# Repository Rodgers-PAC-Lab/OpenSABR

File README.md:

# OpenSABR

OpenSABR stands for "Open-source System for Auditory Brainstem Response".
This repository was previously named "ABR2025".

## Introduction

This repository contains code to implement the ABR measuring system described
in [Gargiullo et al](https://www.biorxiv.org/content/10.64898/2025.12.17.694771v1), 
as well as the analysis scripts needed to replicate the figures in that paper.

The repository is structured as follows:
- `./` - The toplevel directory, containing this README file
- `./hardware_designs` - Design files, bill of materials, and other information about 
physically building the system.
- `./src/opensabr` - source code for analysis and GUI. Import like `import opensabr`
- `./src/opensabr/gui` - A Python module for running the graphical user interface (GUI) 
to take ABR data. It can be imported like `import opensabr.gui`. This code is 
run on a desktop PC connected to the ABR measuring system hardware.
- `./scripts` - A folder of demo scripts that generate the figures in the
paper, using data that we collected and have shared on Zenodo. These scripts 
are meant to be run one at a time, not imported and called by other scripts. 

## Requirements

We used Python 3.11. Newer versions may also work but we did not test them.
- pyproject.toml contains a list of the required dependencies
- requirements-lock.txt includes the exact versions we used

For the analysis scripts (but not the GUI), the following repository is 
required. It should be on your PYTHONPATH so that it can be imported using
the syntax `import my`.
- `git clone git@github.com:Rodgers-PAC-Lab/my.git`

## Instructions

To build the hardware, refer to the file `./hardware_designs/README.md` for finding code and design files, then refer to the file `OpenSABR Build Guide.pdf` for assembly instructions. 

To run the GUI and measure ABR, refer to the file `./src/opensabr/gui/README`.

To run the analysis scripts and regenerate the figures included in the paper,
refer to the file `./scripts/README`.

## Installation of OpenSABR

A note about our package management approach:
- Repositories that are install-able (i.e., using a method like `pip install` or `python setup.py`) are cloned into `~/installed`
- Repositories that need to be importable (like `import reponame`) but are not install-able are cloned into `~/dev`, which is a directory on `$PYTHONPATH`. Two examples of repositories like this are ABRA and Rodgers-PAC-Lab:my.git

The reason for this distinction is because it can cause errors to mix these two kinds of repositories in the same directory.

### Clone the OpenSABR repo

Run the following commands:

```
cd ~/installed
git clone git@github.com:Rodgers-PAC-Lab/OpenSABR
cd OpenSABR
```

Then pick one of the following installation approaches.
- Option A is easier and does not pin any versions of dependencies, so you will get the newest available
- Option B will download the exact versions of the repositories we used. This is mainly useful for reproducing our results exactly. This approach will only work on linux, since that is what we used.

### Option A: Typical install (no version pins)

```
conda create -n opensabr -c conda-forge python=3.11 pip ipython
conda activate opensabr
conda install -c conda-forge numpy scipy pandas matplotlib tqdm pyqt pyqtgraph pyserial pyarrow seaborn
pip install -e . --no-deps
```

### Option B: Reproducible install from lock (linux-64 only)

```
conda create -n opensabr --file opensabr-conda-lock.txt
conda activate opensabr
pip install -e . --no-deps
```

Now you have installed opensabr. Try `import opensabr` to be sure.

You can stop here if you all you want to do is run or use OpenSABR. You only have to continue if you want to reproduce the comparisons to ABRpresto and ABRA that were made in the paper.

## Installation of other ABR software used as a comparison in the paper

In the paper we also compared our analysis software to two others. If you wish to reproduce this comparison, you will need to install them.

- ABRA, installed into a separate conda environment called "abra"
- ABRpresto, installed into a separate conda environment called "abrpresto"

You do not need to install these others if you just want to run OpenSABR.

### Installing ABRpresto

This is an "install-able" module. 

#### Clone repo

Run the following to install our fork. Our demo scripts require the use of our fork, which contains only minor modifications.

```
cd ~/installed 
git clone git@github.com:Rodgers-PAC-Lab/ABRpresto # our fork
cd ABRpresto
git checkout dev # our branch with fixes
```

Then pick one of the following installation approaches, A (flexible) or B (reproducible), analogous to the options above.

#### Option A: Typical install (no version pins)

```
conda create -n abrpresto -c conda-forge python=3.11 ipython pip
conda activate abrpresto
conda install -c conda-forge numpy scipy pandas matplotlib setuptools_scm pyarrow tqdm
pip install -e . --no-deps
```

#### Option B: Reproducible install from lock (linux-64 only)

```
conda create -n abrpresto --file abrpresto-conda-lock.txt
conda activate abrpresto
pip install -e . --no-deps
```

Now ABRpresto should be installed. Check with `import abrpresto`

### Installing ABRA

This is not an "install-able" module, but it is importable, so it need to go on PYTHONPATH.

#### Clone repo (must be under ~/dev or some location on PYTHONPATH)

```
cd ~/dev
git clone git@github.com:Rodgers-PAC-Lab/abranalysis # our fork
cd abranalysis
git checkout dev # our branch with fixes
```

As above, pick Option A or B.

#### Option A: Typical install (no version pins)

```
conda create -n abra -c conda-forge python=3.11 ipython pip
conda activate abra
conda install -c conda-forge numpy scipy pandas scikit-learn pytorch=*=cpu* keras tensorflow streamlit easydict "altair<5" pyarrow matplotlib tqdm
conda env config vars set PYTHONPATH=$HOME/dev
conda deactivate && conda activate abra   # reload so PYTHONPATH takes effect
```

#### Option B: Reproducible install from lock (linux-64 only)

```
conda create -n abra --file abra-conda-lock.txt
conda activate abra
conda env config vars set PYTHONPATH=$HOME/dev
conda deactivate && conda activate abra   # reload so PYTHONPATH takes effect
```

Now ABRA should be installed. Check with `import abranalyais`

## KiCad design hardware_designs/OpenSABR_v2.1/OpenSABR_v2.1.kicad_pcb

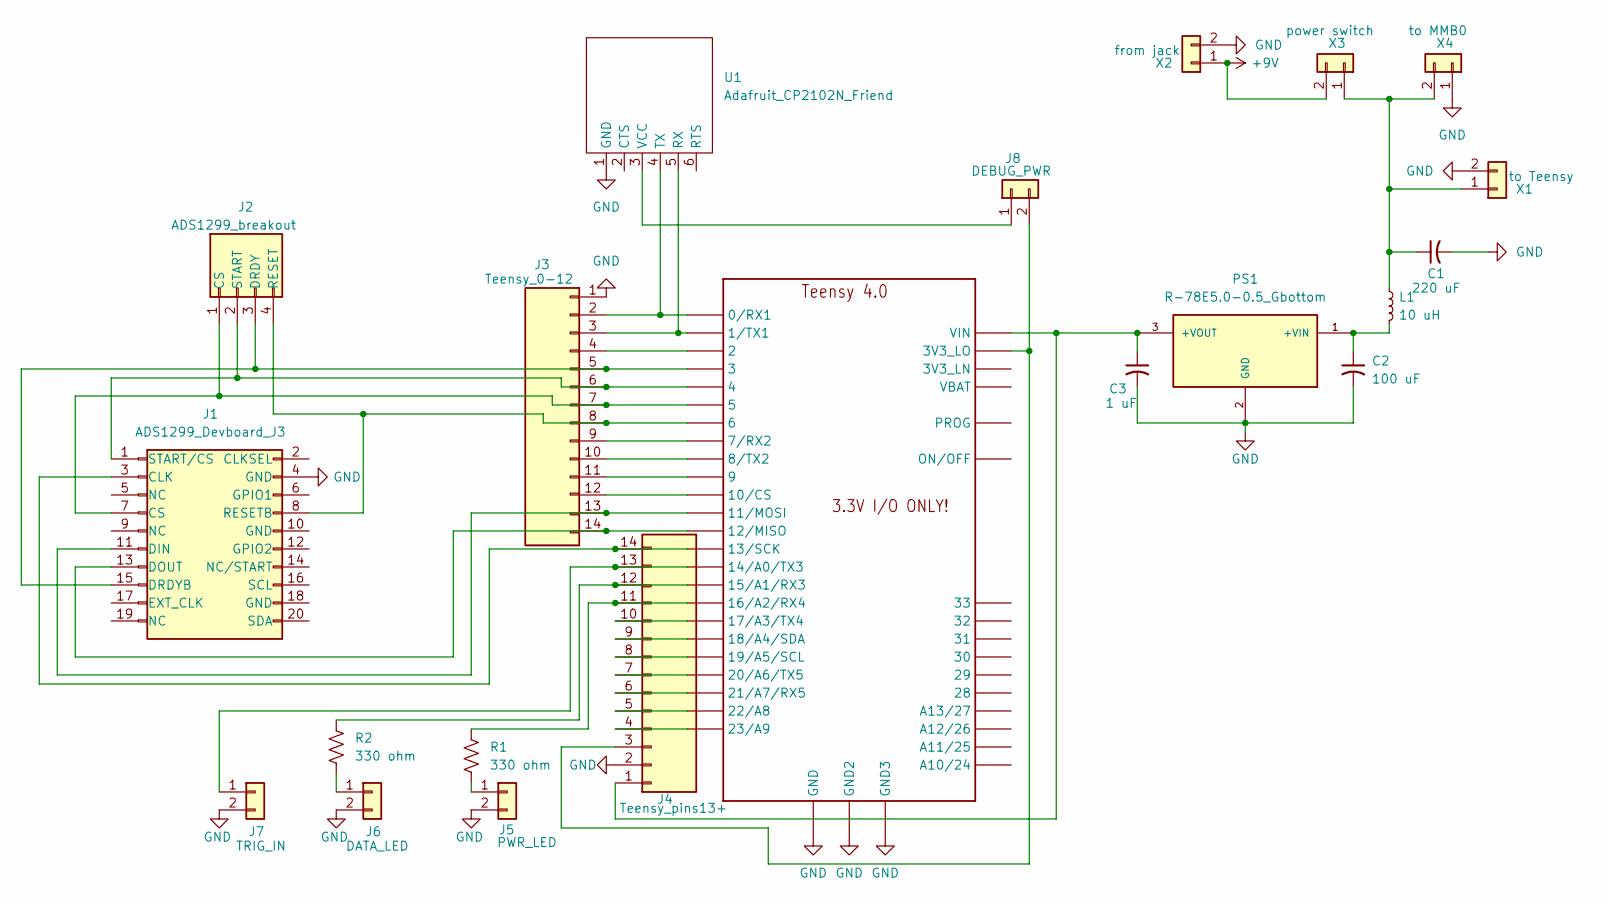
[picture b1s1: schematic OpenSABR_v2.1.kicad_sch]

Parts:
1: TEENSY_4.0_WITH_24-33
C1: 220 uF; CP_Radial_D10.0mm_P5.00mm
C2: 100 uF; CP_Radial_D8.0mm_P3.80mm
C3: 1 uF; CP_Radial_D7.5mm_P2.50mm
J1: ADS1299_Devboard_J3; IDC-Header_2x10_P2.54mm_Vertical
J2: ADS1299_breakout; PinSocket_1x04_P2.54mm_Vertical
J3: Teensy_0-12; PinHeader_1x14_P2.54mm_Vertical
J4: Teensy_pins13+; PinHeader_1x14_P2.54mm_Vertical
J5: PWR_LED; PinHeader_1x02_P2.54mm_Vertical
J6: DATA_LED; PinHeader_1x02_P2.54mm_Vertical
J7: TRIG_IN; PinHeader_1x02_P2.54mm_Vertical
J8: DEBUG_PWR; PinHeader_1x02_P2.54mm_Vertical
L1: 10 uH; L_Axial_L9.5mm_D4.0mm_P15.24mm_Horizontal_Fastron_SMCC
PS1: R-78E5.0-0.5_Gbottom; CONV_R-78E5.0-0.5; PARTREV v4
R1, R2: 330 ohm; R_Axial_DIN0207_L6.3mm_D2.5mm_P10.16mm_Horizontal
U1: Adafruit_CP2102N_Friend
X1: to Teensy; JST_XH_B2B-XH-A_1x02_P2.50mm_Vertical
X2: from jack; JST_XH_B2B-XH-A_1x02_P2.50mm_Vertical
X3: power switch; JST_XH_B2B-XH-A_1x02_P2.50mm_Vertical
X4: to MMB0; JST_XH_B2B-XH-A_1x02_P2.50mm_Vertical

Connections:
+9V: X2.1, X3.2
GND: 1.GND, 1.GND2, 1.GND3, C1.2, C2.2, C3.2, J1.4 (GND), J3.1, J4.2, J5.2, J6.2, J7.2, PS1.2 (GND), U1.1 (GND), X1.2, X2.2, X4.1
unnamed: 1.0/RX (0/RX1), J3.2, U1.4 (TX)
unnamed: 1.1/TX (1/TX1), J3.3, U1.5 (RX)
unnamed: 1.7 (7/RX2), J3.9
unnamed: 1.8 (8/TX2), J3.10
unnamed: 1.14/A0 (14/A0/TX3), J4.13, J7.1
unnamed: 1.15/A1 (15/A1/RX3), J4.12, R2.1
unnamed: 1.16/A2 (16/A2/RX4), J4.11, R1.1
unnamed: 1.17/A3 (17/A3/TX4), J4.10
unnamed: 1.20/A6 (20/A6/TX5), J4.7
unnamed: 1.21/A7 (21/A7/RX5), J4.6
unnamed: 1.13/SCK, J1.3 (CLK), J4.14
unnamed: 1.5, J1.7 (CS), J2.1 (CS), J3.7
unnamed: 1.11/MOSI, J1.11 (DIN), J3.13
unnamed: 1.12/MISO, J1.13 (DOUT), J3.14
unnamed: 1.3, J1.15 (DRDYB), J2.3 (DRDY), J3.5
unnamed: 1.6, J1.8 (RESETB), J2.4 (RESET), J3.8
unnamed: 1.4, J1.1 (START/CS), J2.2 (START), J3.6
unnamed: 1.2, J3.4
unnamed: 1.9, J3.11
unnamed: 1.10/CS, J3.12
unnamed: 1.VIN, C3.1, J4.1, PS1.3 (+VOUT)
unnamed: 1.3V3_LO, J4.3, J8.2
unnamed: 1.23/A9, J4.4
unnamed: 1.22/A8, J4.5
unnamed: 1.19/A5/SCL, J4.8
unnamed: 1.18/A4/SDA, J4.9
unnamed: J5.1, R1.2
unnamed: J6.1, R2.2
unnamed: J8.1, U1.3 (VCC)
unnamed: C2.1, L1.2, PS1.1 (+VIN)
unnamed: C1.1, L1.1, X1.1, X3.1, X4.2

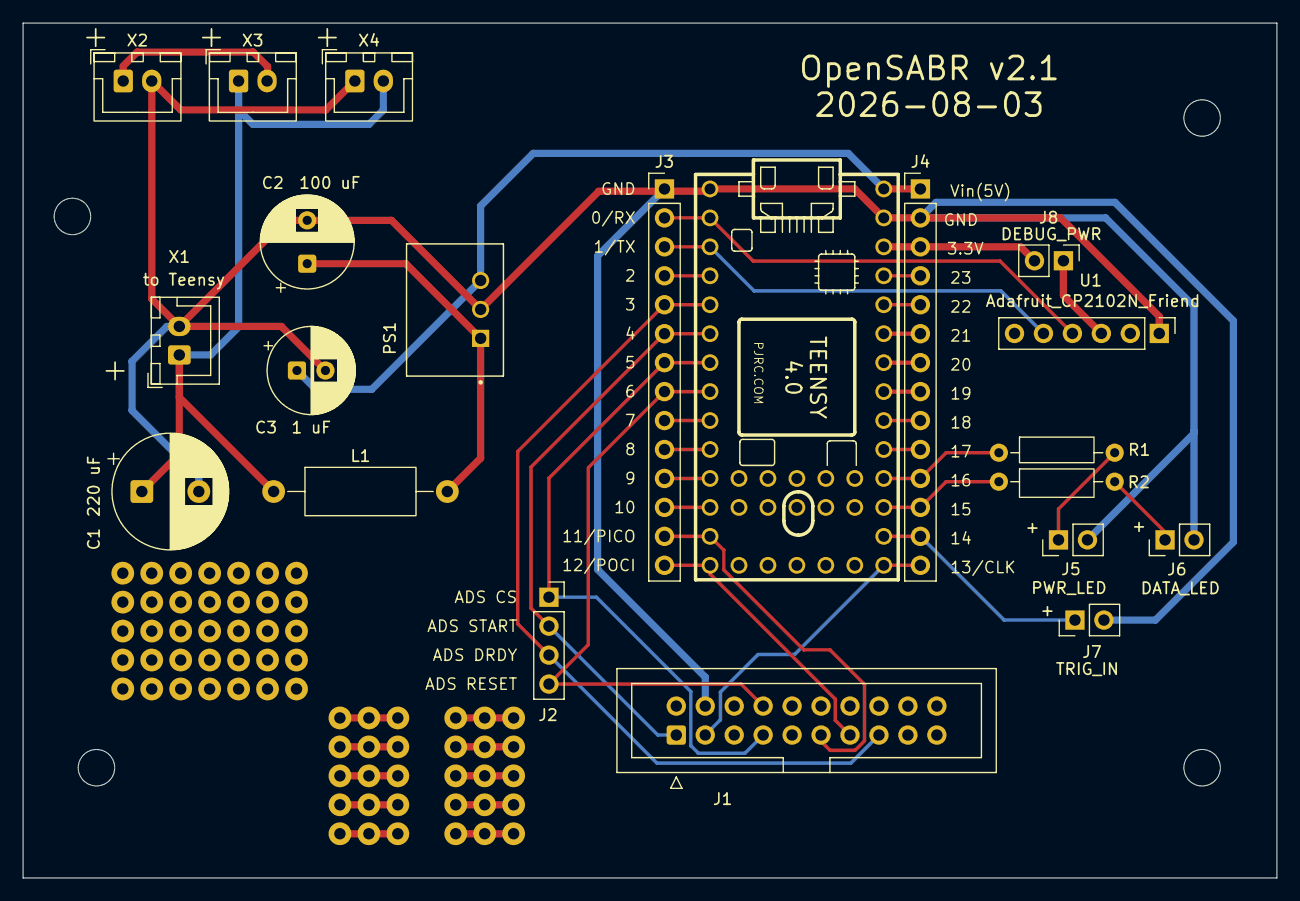
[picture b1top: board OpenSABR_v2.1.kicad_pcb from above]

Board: 2 copper layers, 110.0 x 75.0 mm, 85 parts (0 on the bottom side), 33 nets.

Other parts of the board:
3, 4, 5, 6, 7, 8, 9, 9#2, 11, 12, 13, 14, 15, 16, 17, 17#2, 19, 20, 21, 22, 23, 24, 25, 25#2, 26, 27, 28, 29, 30, 31, 32, 33, 35, 36, 37, 38, 39, 40, 41, 41#2, 43, 44, 45, 46, 47, 48, 49, 57, 58, 59, 60, 61, 62, 63, 64, 65, 66, 67, 68, 69, 70, 71, 72, 73: (no value)
